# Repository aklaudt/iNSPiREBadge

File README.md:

# DigiGirlz Badge
This is a simple electronic name badge designed by Omnitech Inc for the Microsoft DigiGirlz 2020 event in Sioux Falls South Dakota. The board is based on an Atmel 328p microcontroller, and has a 128x64 oled display, powered by a CR2032 battery.

## Requirements
* This repository [Download Here](https://github.com/ad3154/DigiGirlzBadge/archive/master.zip)
* DigiGirlz Badge
* USBTinyISP Programmer
* USBTinyISP Driver [Download](https://github.com/adafruit/Adafruit_Windows_Drivers/releases/download/2.4.0.0/adafruit_drivers_2.4.0.0.exe)
* Arduino IDE [Download Here](https://www.arduino.cc/download_handler.php)
* Adafruit SSD1306 Library [How to install libraries](https://www.arduino.cc/en/guide/libraries)
* Low-Power Library [How to install libraries](https://www.arduino.cc/en/guide/libraries)
* (optional) CR2032 Battery
* (optional) [LCD Assistant](http://en.radzio.dxp.pl/bitmap_converter/)

## Instructions
* Install all of the software listed above, including Arduino and the driver.
* Install the arduino libraries. See [Here for instructions](https://www.arduino.cc/en/guide/libraries)
* Plug the programmer into your computer via the included USB cable.
* Connect your badge to the programmer using the included 6 pin ribbon cable.
* The badge will power on if connected properly. If it does not, you may need to reverse the ribbon cable.
* Open either of the example .ino files in the Arduino IDE. 
* Edit the code if you wish
* Click "Sketch" -> "Upload Using Programmer". This may take some time. Do not unplug the badge.
* Once the upload is complete, your code will run, and the screen will change.
* See the powerpoint presentation in the repository for more detailed instructions.

## More Information
You can learn more about DigiGirlz [from Microsoft's website](https://www.microsoft.com/en-us/diversity/programs/digigirlz/default.aspx), and you can learn more about Omnitech [here](https://www.omnitech-inc.com).

My personal website: https://delgrossoengineering.com

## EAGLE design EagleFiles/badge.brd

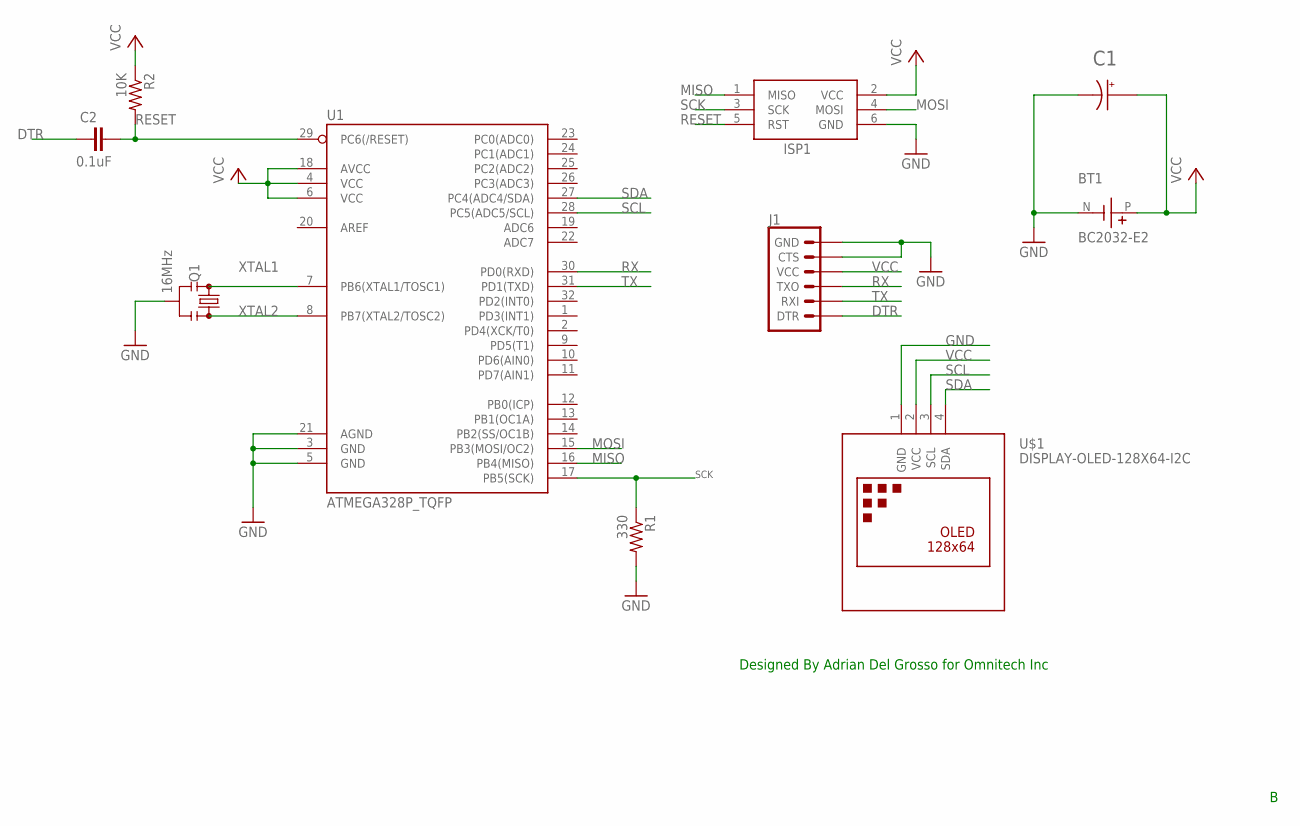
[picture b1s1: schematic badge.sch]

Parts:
BT1: BC2032-E2; MPD_BC2032-E2
C1: RNE1C101MDS1PX; CAPPRD200W50D500H1000
C2: 0.1uF; 0402
ISP1: AVRISP-6; AVRISP
J1: 6_PIN_SERIAL_TARGETLONGPADS; 1X06_LONGPADS
Q1: 16MHz; RESONATOR-SMD-3.2X1.3
R1: 330; R0603
R2: 10K; R0603
U1: ATMEGA328P_TQFP; TQFP32-08
U$1: DISPLAY-OLED-128X64-I2C

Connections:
DTR: C2.1, J1.1 (DTR)
GND: BT1.N, C1.2 (N), ISP1.6 (GND), J1.5 (CTS), J1.6 (GND), Q1.2, R1.2, U1.3 (GND), U1.5 (GND), U1.21 (AGND), U$1.1 (GND)
MISO: ISP1.1 (MISO), U1.16 (PB4(MISO))
MOSI: ISP1.4 (MOSI), U1.15 (PB3(MOSI/OC2))
RESET: C2.2, ISP1.5 (RST), R2.2, U1.29 (PC6(/RESET))
RX: J1.3 (TXO), U1.30 (PD0(RXD))
SCK: ISP1.3 (SCK), R1.1, U1.17 (PB5(SCK))
SCL: U1.28 (PC5(ADC5/SCL)), U$1.3 (SCL)
SDA: U1.27 (PC4(ADC4/SDA)), U$1.4 (SDA)
TX: J1.2 (RXI), U1.31 (PD1(TXD))
VCC: BT1.P, C1.1, ISP1.2 (VCC), J1.4 (VCC), R2.1, U1.4 (VCC), U1.6 (VCC), U1.18 (AVCC), U$1.2 (VCC)
XTAL1: Q1.1, U1.7 (PB6(XTAL1/TOSC1))
XTAL2: Q1.3, U1.8 (PB7(XTAL2/TOSC2))

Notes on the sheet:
Designed By Adrian Del Grosso for Omnitech Inc

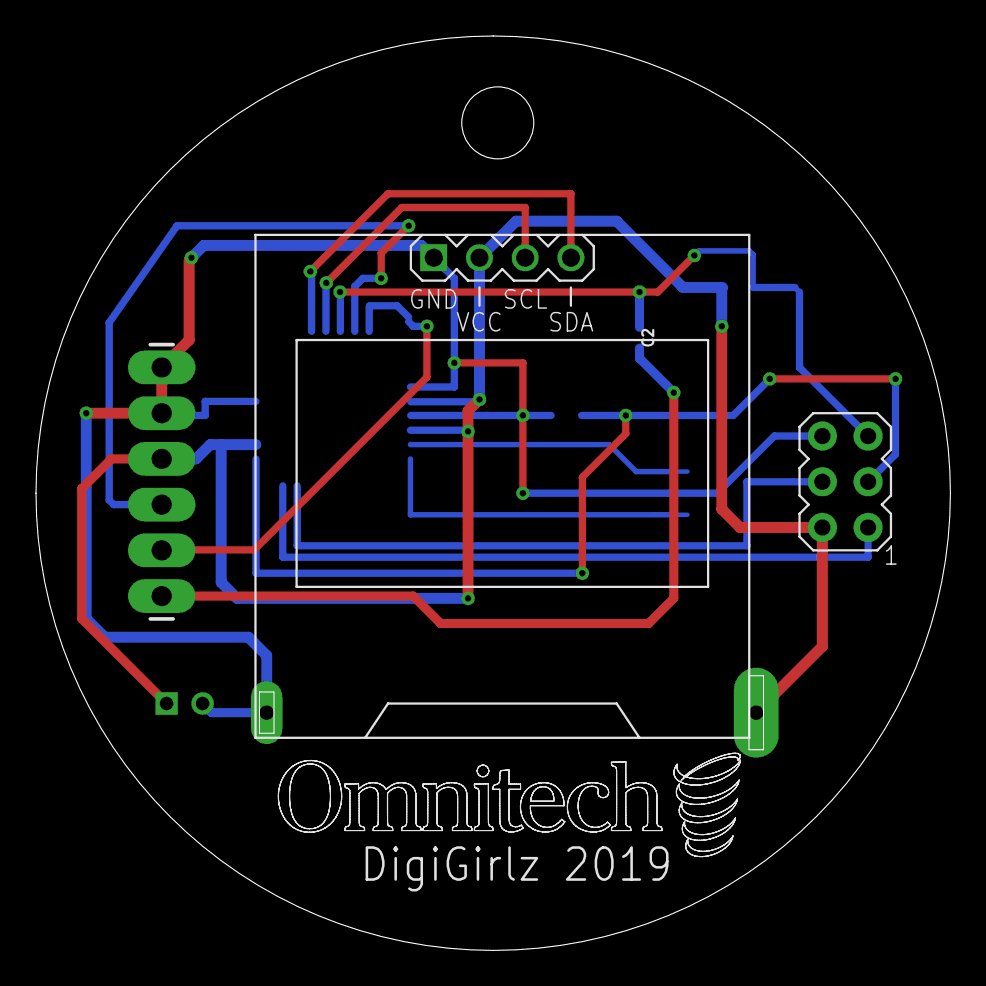
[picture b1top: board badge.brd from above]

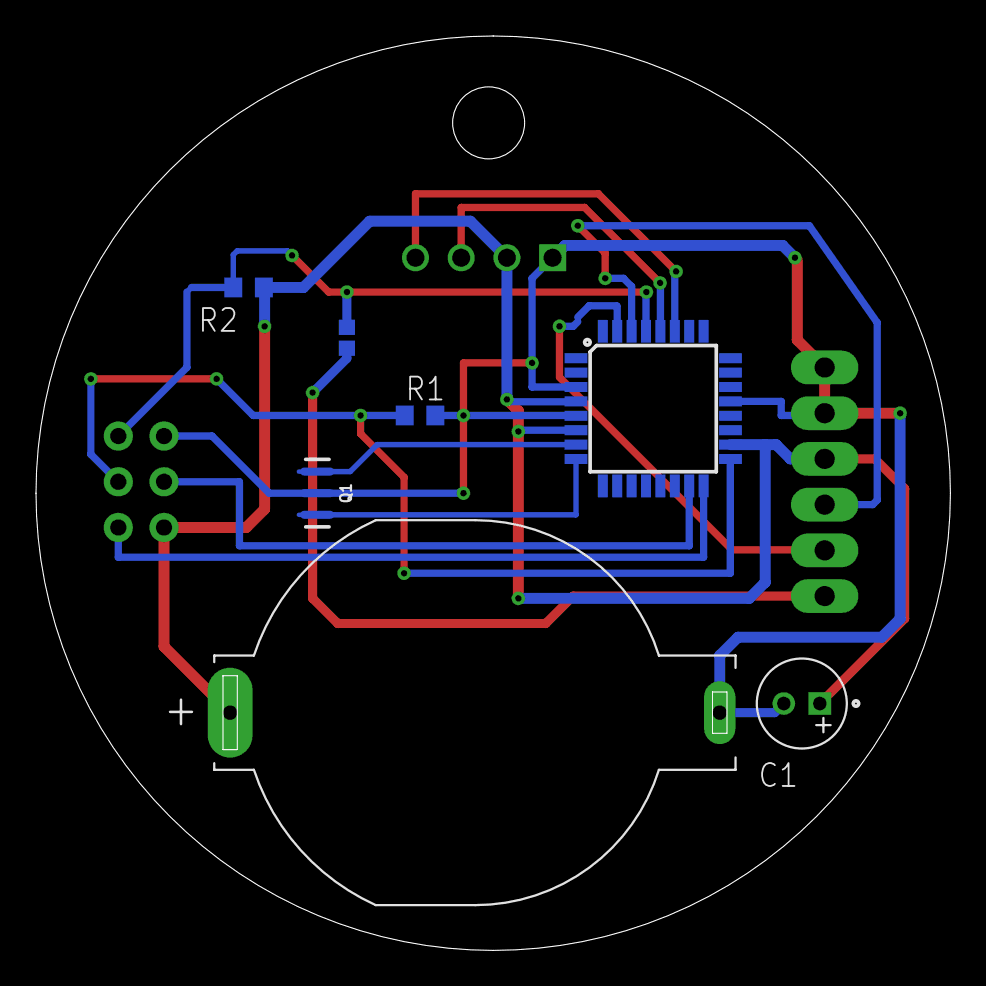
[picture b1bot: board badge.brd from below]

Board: 2 copper layers, 50.8 x 50.8 mm, 10 parts (7 on the bottom side), 13 nets.

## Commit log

2019-11-07 Added first revision of Eagle Files
2020-01-16 Added screen documentation, updated Eagle Files, added starter Arduino sketch
2020-03-05 Added example project, reorganized folders
2020-03-05 Added Presentation
2020-03-05 Update README to add LCD assitant link
2023-02-28 Update to Inspire branding
2023-03-21 Updated presentation

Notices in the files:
parts and their libraries:
SparkFun-Clocks: Licensing: Creative Commons ShareAlike 4.0 International - https://creativecommons.org/licenses/by-sa/4.0
diy-modules: Released under the Creative Commons Attribution 4.0 International License: http://creativecommons.org/licenses/by/4.0
